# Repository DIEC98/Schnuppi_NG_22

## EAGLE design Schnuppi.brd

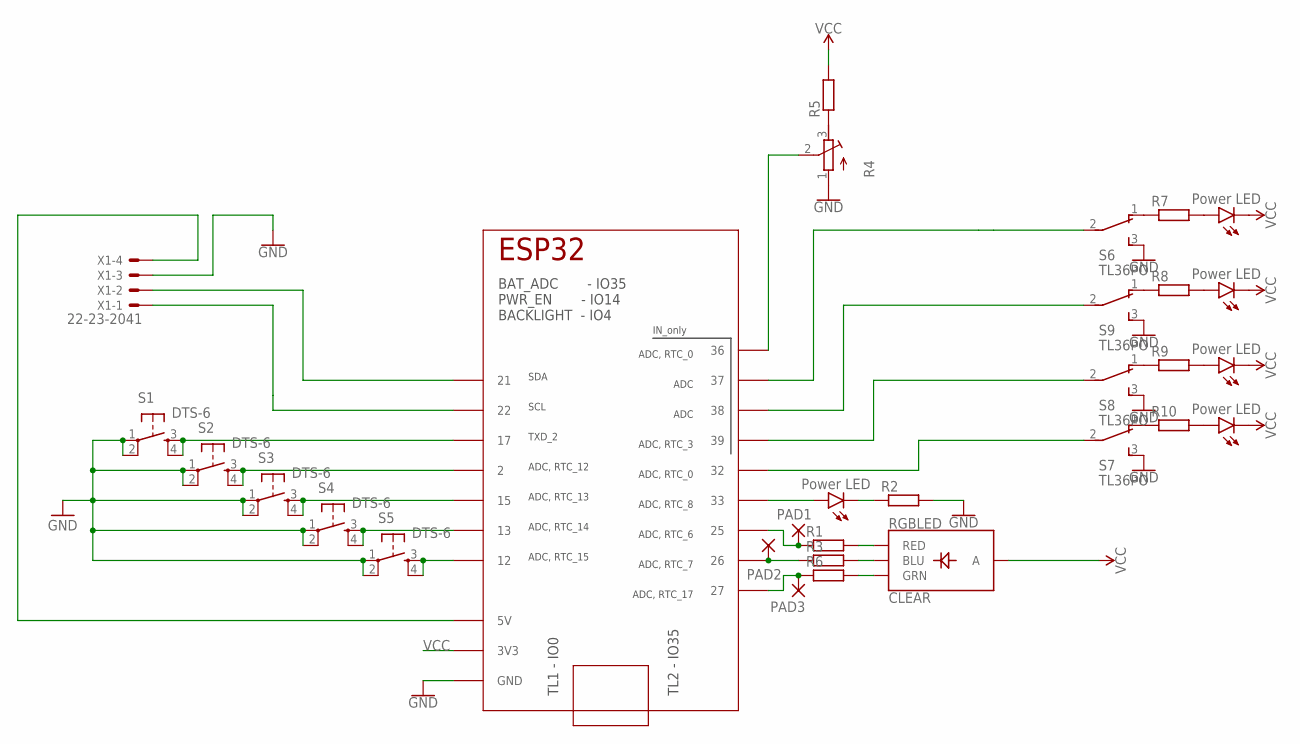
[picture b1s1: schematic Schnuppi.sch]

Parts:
IC1: TTGO_DISP; TTGO_DISP_DEFAULT
P1, P2, P3, P4, P5: Power LED; LED_5MM
PAD1, PAD2, PAD3: SMD5; SMD2,54-5,08
R1, R2, R3, R5, R6, R7, R8, R9, R10: R-EU_V234/12; V234/12
R4: R-TRIMM64Y; RTRIM64Y
RGBLED: CLEAR; LED-RGB-THRU
S1, S2, S3, S4, S5: DTS-6
S6, S7, S8, S9: TL36PO; TL3XPO
X1: 22-23-2041

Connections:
GND: IC1.GND_1 (GND), IC1.GND_2 (GND), IC1.GND_3 (GND), IC1.GND_4 (GND), IC1.GND_5 (GND), R2.2, R4.1 (A), S1.1, S1.2, S2.1, S2.2, S3.1, S3.2, S4.1, S4.2, S5.1, S5.2, S6.3 (S), S7.3 (S), S8.3 (S), S9.3 (S)
unnamed: IC1.12, S5.3, S5.4
unnamed: IC1.13, S4.3, S4.4
unnamed: IC1.15, S3.3, S3.4
unnamed: IC1.2, S2.3, S2.4
unnamed: IC1.17, S1.3, S1.4
unnamed: R4.3 (E), R5.1
unnamed: IC1.36, R4.2 (S)
unnamed: IC1.25, PAD1.1, R1.1
unnamed: IC1.27, PAD3.1, R6.1
unnamed: IC1.26, PAD2.1, R3.1
unnamed: IC1.33, P2.A
unnamed: P2.K (C), R2.1
unnamed: IC1.22, X1.1
unnamed: R1.2, RGBLED.1 (RED)
unnamed: R3.2, RGBLED.4 (BLU)
unnamed: R6.2, RGBLED.3 (GRN)
unnamed: IC1.5V, X1.4
unnamed: IC1.37, S6.2
unnamed: IC1.39, S8.2
unnamed: IC1.32, S7.2
unnamed: IC1.38, S9.2
unnamed: R10.1, S7.1 (O)
unnamed: R9.1, S8.1 (O)
unnamed: R8.1, S9.1 (O)
unnamed: R7.1, S6.1 (O)
unnamed: P1.A, R7.2
unnamed: P3.A, R8.2
unnamed: P4.A, R9.2
unnamed: P5.A, R10.2
unnamed: IC1.21, X1.2
VCC: IC1.3V3_1 (3V3), IC1.3V3_2 (3V3), P1.K (C), P3.K (C), P4.K (C), P5.K (C), R5.2, RGBLED.2 (A)

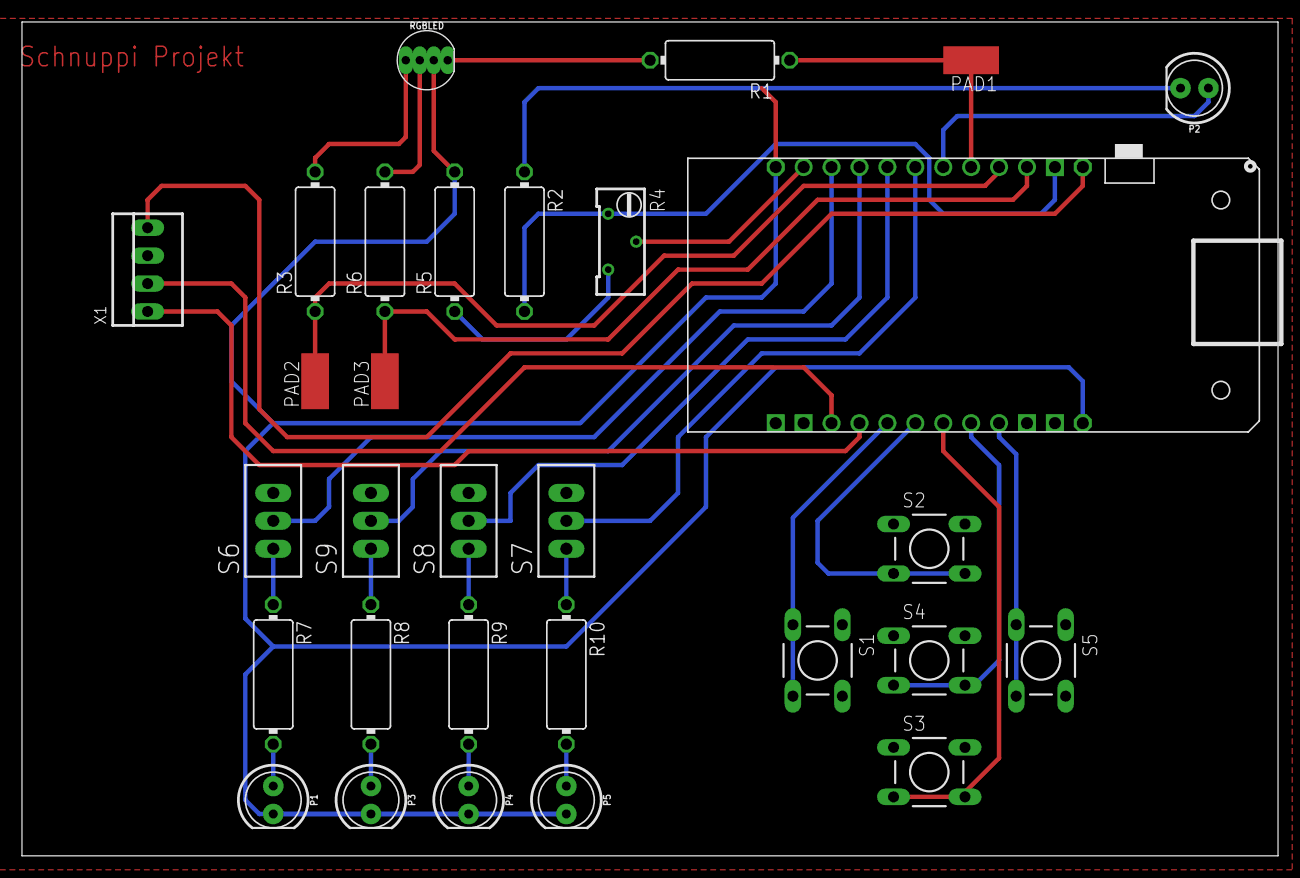
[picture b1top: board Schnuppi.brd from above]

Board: 2 copper layers, 114.3 x 75.9 mm, 30 parts (0 on the bottom side), 32 nets.

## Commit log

2022-07-08 minor changes
2022-07-08 addes test file
2022-07-08 test gelöscht
2022-07-08 test2
2022-07-08 test3
2022-07-08 test4
2022-07-08 test5
2022-07-08 test6
2022-07-08 test
2022-07-08 test1
2022-07-08 alskjdflsaf
2022-07-08 sjdf
2022-07-08 kkkkk
2022-07-08 ksjdfksjfkjsfjslkjflsjlsfjkl
2022-07-11 Test Lehrschlag
2022-08-05 Board Konzept 1 FUMM
2022-08-05 Dokumentation hinzugefügt

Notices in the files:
parts and their libraries:
SparkFun-LED: Licensing: Creative Commons ShareAlike 4.0 International - https://creativecommons.org/licenses/by-sa/4.0
